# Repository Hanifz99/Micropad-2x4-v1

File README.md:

# Micropad 2x4 v1

A compact, customizable keypad with programmable buttons that automate complex commands or shortcuts with a single press.(this project need continue to build)

## Features
- 128x32 OLED Display
- 3 SK6812 MINI-E LEDs
- 8 Programmable Keys

## CAD Model

These are the CAD models designed in Fusion 360.

.png)
.png)
.png)
.png)

## PCB

The PCB was designed in KiCad.

## Firmware Overview

This macropad uses QMK firmware for mapping the 8 keys. You can customize them for playing music, videos, or other shortcuts.

## Bill of Materials (BOM)

Here is everything you need to build this macropad:

- 8x Cherry MX Switches
- 8x Keycaps
- 4x M2.5 Bolts
- 8x Diodes
- 3x SK6812 MINI-E LEDs
- 1x 0.91" 128x32 OLED Display
- 1x XIAO RP2040
- 1x Case (2 parts)

## How to Build

1. Assemble the PCB with components from the BOM.
2. Flash the firmware using QMK.
3. Mount switches and keycaps.
4. Enjoy your custom macropad!

## Contributing

Feel free to open issues or pull requests for improvements.

## Acknowledgments

Thank you for checking out my project! UwU
Thanks hackclub for supporting my project !!

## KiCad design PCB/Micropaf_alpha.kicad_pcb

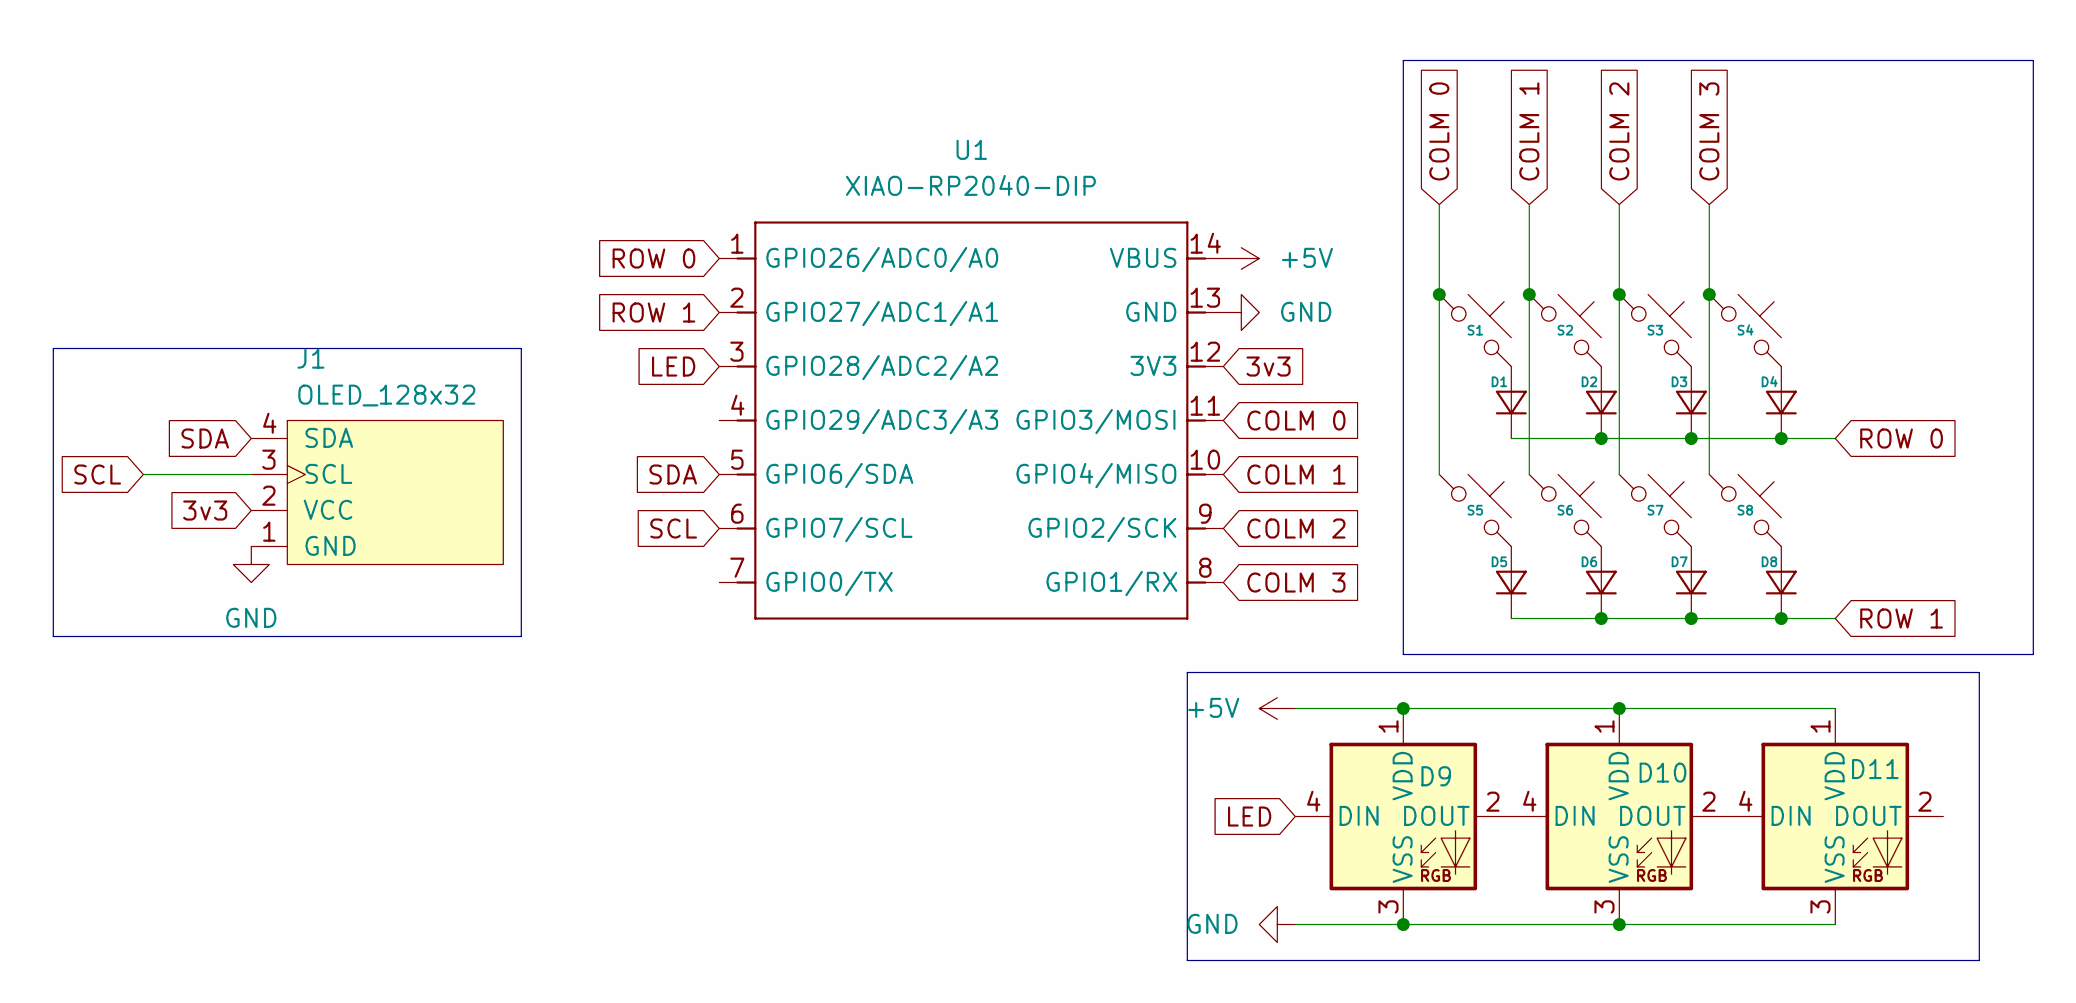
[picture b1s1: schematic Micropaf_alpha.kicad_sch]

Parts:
D1, D2, D3, D4, D5, D6, D7, D8: Diode_DO-35
D9, D10, D11: LED_SK6812MINI; LCSC C5149201
J1: OLED_128x32
S1, S2, S3, S4, S5, S6, S7, S8: MX_PCB_1.00u
U1: XIAO-RP2040-DIP; Seeed_XIAO_RP2040

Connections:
3v3: J1.2 (VCC), U1.12 (3V3)
+5V: D9.1 (VDD), D10.1 (VDD), D11.1 (VDD), U1.14 (VBUS)
COLM 0: S1.1, S5.1, U1.11 (GPIO3/MOSI)
COLM 1: S2.1, S6.1, U1.10 (GPIO4/MISO)
COLM 2: S3.1, S7.1, U1.9 (GPIO2/SCK)
COLM 3: S4.1, S8.1, U1.8 (GPIO1/RX)
GND: D9.3 (VSS), D10.3 (VSS), D11.3 (VSS), J1.1 (GND), U1.13 (GND)
LED: D9.4 (DIN), U1.3 (GPIO28/ADC2/A2)
unnamed: D1.2 (A), S1.2
unnamed: D2.2 (A), S2.2
unnamed: D3.2 (A), S3.2
unnamed: D4.2 (A), S4.2
unnamed: D5.2 (A), S5.2
unnamed: D6.2 (A), S6.2
unnamed: D7.2 (A), S7.2
unnamed: D8.2 (A), S8.2
unnamed: D9.2 (DOUT), D10.4 (DIN)
unnamed: D10.2 (DOUT), D11.4 (DIN)
ROW 0: D1.1 (K), D2.1 (K), D3.1 (K), D4.1 (K), U1.1 (GPIO26/ADC0/A0)
ROW 1: D5.1 (K), D6.1 (K), D7.1 (K), D8.1 (K), U1.2 (GPIO27/ADC1/A1)
SCL: J1.3 (SCL), U1.6 (GPIO7/SCL)
SDA: J1.4 (SDA), U1.5 (GPIO6/SDA)

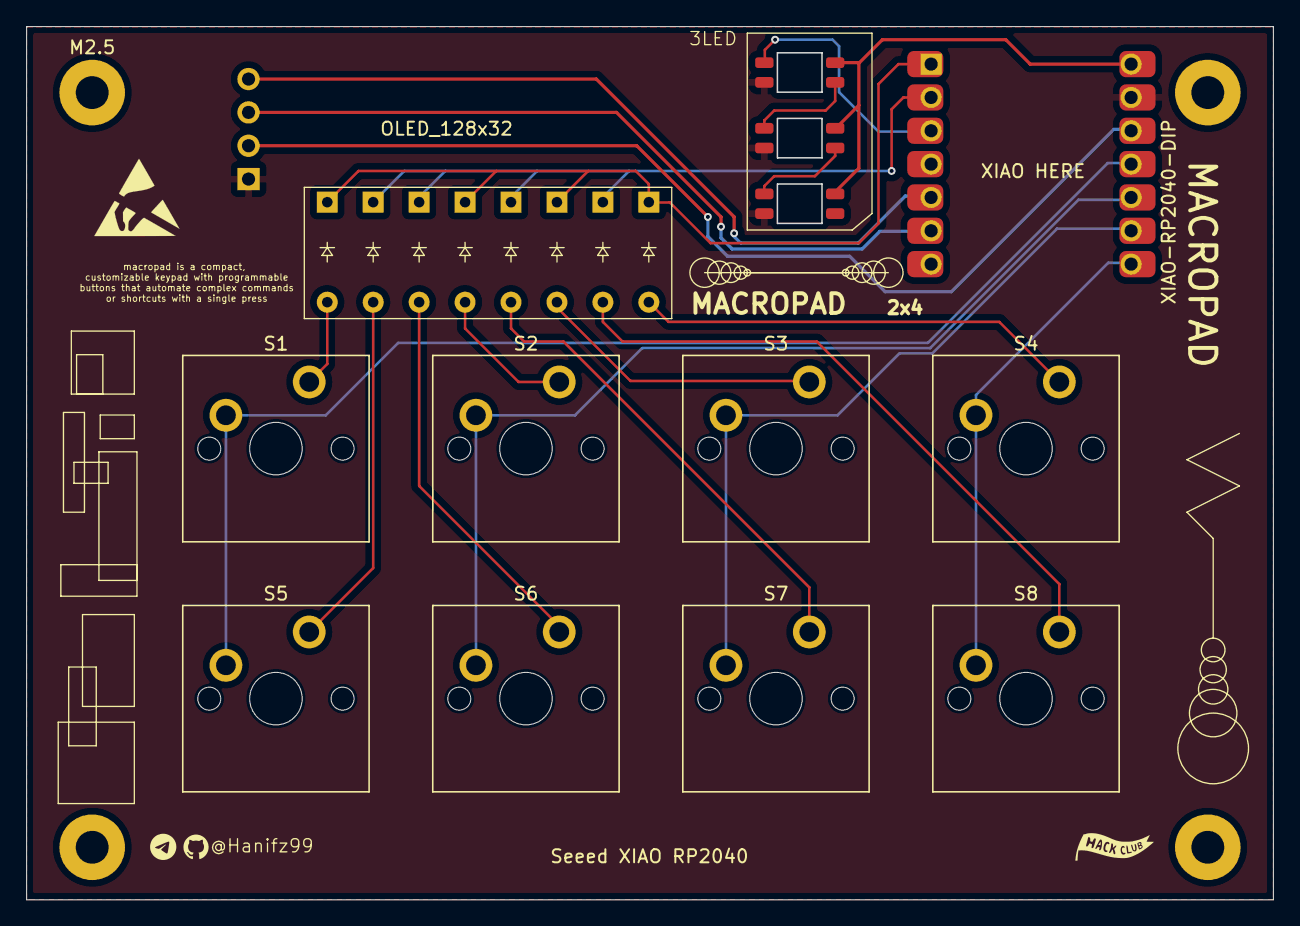
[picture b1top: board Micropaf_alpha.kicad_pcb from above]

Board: 2 copper layers, 94.9 x 66.5 mm, 22 parts (0 on the bottom side), 22 nets.

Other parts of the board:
M2.5: MountingHole_2.5mm_Pad

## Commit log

2025-12-31 Update README with image instructions
2025-12-31 Add assets folder with screenshots from Fusion360 and KiCad
2025-12-31 Add CAD model image to README
2025-12-31 Add all CAD model images from fusion360 folder
2025-12-31 Add PCB images from kicad folder to README
2025-12-31 Improve README: fix grammar, add sections, and enhance structure
2025-12-31 Add GPL3 license badge to README
2025-12-31 Add GPL3 logo from GNU assets to README
2025-12-31 Update README and add GNU assets
2025-12-31 Add new KiCad PCB photos to README
2026-01-06 upload step
